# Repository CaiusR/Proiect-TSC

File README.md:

# InkTime — Open-Source Smartwatch

**InkTime** is a cheap, low-power, open-source smartwatch built around the Nordic **nRF52840** SoC with a **1.54" e-paper display**, designed for BLE connectivity and mass production at JLCPCB.

This repository contains the full EVT (Engineering Validation) deliverables: schematic, PCB layout, manufacturing files, 3D mechanical assembly and documentation.

---

## Table of Contents

1. [Block Diagram](#block-diagram)
2. [Bill of Materials](#bill-of-materials)
3. [Hardware Description](#hardware-description)
4. [Power Budget & Battery Life](#power-budget--battery-life)
5. [nRF52840 Pin Assignment](#nrf52840-pin-assignment)
6. [PCB Design Notes](#pcb-design-notes)
7. [Protection & Safety](#protection--safety)
8. [Mechanical Assembly](#mechanical-assembly)
9. [Manufacturing](#manufacturing)
10. [Repository Structure](#repository-structure)
11. [Development Log](#development-log)
12. [Design Decisions](#design-decisions)
13. [Renderings](#renderings)
14. [Build Instructions](#build-instructions)
15. [License](#license)

---

## Block Diagram

```
                                        ┌────────────────────┐
                                        │  E-Paper Display   │
                                        │  1.54"  200×200    │
                                        │  (WSH-12561)       │
                                        └──────────┬─────────┘
                                                   │
                                      SPI (MOSI, SCK) + CS/DC/RST/BUSY
                                                   │
  ┌─────────────┐  VBUS (5V)   ┌─────────┐  VREG  ┌─────────────────────┐      I²C Bus
  │   USB-C     │──────────────│ BQ25180 │────────│   RT6160AWSC        │─────────┬───────────────┐
  │ KH-TYPE-C   │              │  LiPo   │        │   DC/DC Buck-Boost  │   3V3   │               │
  │   -16P      │   D+ / D-    │ Charger │        │   → 3.3 V           ├─────────┤               │
  └──────┬──────┘──────┐       └────┬────┘        └─────────────────────┘         │               │
         │             ▼            │ BAT                                         │         ┌─────▼─────┐
    ┌────▼────┐    ┌──────┐         ▼                                             │         │  BMA423   │
    │   F1    │    │ USB  │    ┌─────────┐                                        │  I²C    │  IMU      │
    │(fuse 0Ω)│    │ LC6  │    │  LiPo   │              ┌─────────────────────┐   ├────────▶│  Accel.   │
    └─────────┘    │(ESD) │    │ Battery │              │      nRF52840       │   │         │  (3-axis) │
         │        └──────┘    │  3.7V   │              │     (QFN-73)        │   │         └───────────┘
         ▼                    │ 250 mAh │              │                     │   │
    ┌─────────┐   ┌──────┐    └─────────┘              │  ARM Cortex-M4F     │   │         ┌─────────────┐
    │  D_TVS  │   │ TVS  │         │                   │  64 MHz             │   │  I²C    │  MAX17048   │
    │ (MBR0530│   │clamp │         ▼                   │  1 MB Flash         │   ├────────▶│  Fuel Gauge │
    │  clamp) │   └──────┘    ┌─────────┐              │  256 kB RAM         │◀──┘         └─────────────┘
    └─────────┘               │  VBAT   │◀─────────────│                     │
                              │ monitor │              │  BLE 5.0            │             ┌─────────────┐
                              └─────────┘              │  USB 2.0 FS         │   I²C       │  DRV2605    │
                                                       │                     │────────────▶│  Haptic     │
                                                       │  32 MHz + 32 kHz    │             │  Driver     │
                                                       │  Crystals           │             └──────┬──────┘
                                                       └────────┬────────────┘                    │
                                                                │                           OUT+ / OUT−
                                                              RF + matching                        ▼
                                                              (L1, C3, C4, C9)              ┌──────────────┐
                                                                │                           │  Vibration   │
                                                          ┌─────▼──────┐                    │  Motor       │
                                                          │ 2.4 GHz    │                    │  (FIT0774)   │
                                                          │ Chip       │                    └──────────────┘
                                                          │ Antenna    │
                                                          │ (2450AT)   │               ┌──────────────────┐
                                                          └────────────┘               │  3 Buttons       │
                                                                                       │  (EVP-AKE31A)    │
                                                                                       │  UP / ENT / DN   │
                                                                                       └──────────────────┘
```

### Signal summary
- **I²C bus** (400 kHz): RT6160, BQ25180, BMA423, MAX17048, DRV2605 — shared with 3K3 pull-ups on SCL/SDA.
- **SPI bus**: MOSI+SCK → EPD FPC connector only (single slave).
- **USB 2.0 FS**: connects to nRF52840's native USB peripheral via USBLC6 ESD protection.
- **Interrupt lines**: PMIC_INT (BQ25180), ALERT (MAX17048), IMU_INT1/2 (BMA423) with 100K pull-ups.
- **SWD + SWO**: TC2030-IDC pogo-pin connector for debug/programming.

---

## Bill of Materials

Full BOM is in `Manufacturing/InkTime.bom`. Summary of critical components:

### Active Components

| # | Function | Designator | Part | Package | Qty | JLCPCB |
|---|----------|------------|------|---------|:---:|--------|
| 1 | MCU | U1 | nRF52840-QIAA | QFN-73 7×7 | 1 | [C190794](https://jlcpcb.com/partdetail/C190794) |
| 2 | DC/DC Buck-Boost | IC9 | RT6160AWSC | BGA-15 | 1 | [C2682941](https://jlcpcb.com/partdetail/C2682941) |
| 3 | LiPo Charger | IC1 | BQ25180YBGR | BGA-8 | 1 | [C2064810](https://jlcpcb.com/partdetail/C2064810) |
| 4 | IMU (3-axis) | IC3 | BMA423 | LGA-12 2×2 | 1 | [C437656](https://jlcpcb.com/partdetail/C437656) |
| 5 | Fuel Gauge | U3 | MAX17048G+T10 | DFN-8 2×2 | 1 | [C116543](https://jlcpcb.com/partdetail/C116543) |
| 6 | Haptic Driver | IC2 | DRV2605YZFR | BGA-9 | 1 | [C527436](https://jlcpcb.com/partdetail/C527436) |
| 7 | ESD Protection (USB) | D3 | USBLC6-2SC6Y | SOT-23-6 | 1 | [C7519](https://jlcpcb.com/partdetail/C7519) |
| 8 | P-MOSFET (EPD power) | Q1 | DMG2305UX-7 | SOT-23-3 | 1 | [C145093](https://jlcpcb.com/partdetail/C145093) |
| 9 | N-MOSFET (EPD drive) | Q3 | SI1308EDL-T1-GE3 | SOT-323-3 | 1 | [C191043](https://jlcpcb.com/partdetail/C191043) |
| 10 | Schottky (EPD drive) | D2, D4, D5 | MBR0530 | SOD-123 | 3 | [C95872](https://jlcpcb.com/partdetail/C95872) |
| 11 | **TVS clamp (VBUS)** | **D_TVS** | **MBR0530** | **SOD-123** | **1** | **[C95872](https://jlcpcb.com/partdetail/C95872)** |
| 12 | 2.4 GHz Antenna | ANT1 | 2450AT18B100E | 3216 | 1 | [C504989](https://jlcpcb.com/partdetail/C504989) |
| 13 | 32 MHz Crystal | X1 | ±10 ppm | 2016 | 1 | [C255909](https://jlcpcb.com/partdetail/C255909) |
| 14 | 32.768 kHz Crystal | X2 | ±20 ppm | 3215 | 1 | [C181095](https://jlcpcb.com/partdetail/C181095) |

### Connectors

| # | Function | Designator | Part | Qty |
|---|----------|------------|------|:---:|
| 15 | USB-C receptacle | J4 | KH-TYPE-C-16P | 1 |
| 16 | E-paper FPC (24-pin) | J1 | 503480-2400 | 1 |
| 17 | SWD Debug (pogo) | J2 | TC2030-IDC | 1 |

### Passives

| # | Value / Voltage | Designators | Pkg | Qty | JLCPCB |
|---|-----------------|-------------|:---:|:---:|--------|
| 18 | 3V3-domain caps 100 nF | C5, C7, C8, C12, C19, **C_RESET** | 0201 | 6 | [C2181068](https://jlcpcb.com/partdetail/C2181068) |
| 19 | 12 pF (crystal load) | C1, C2, C17, C18 | 0201 | 4 | [C2181049](https://jlcpcb.com/partdetail/C2181049) |
| 20 | RF matching 1 pF / 820 pF / 100 pF | C3, C4, C11 | 0201 | 3 | various |
| 21 | Decoupling 4.7 µF | C6, C14, C20, C21, C43 | 0402 | 5 | [C23733](https://jlcpcb.com/partdetail/C23733) |
| 22 | Bulk 22 µF (3V3) | C25, C33 | 0402 | 2 | [C159770](https://jlcpcb.com/partdetail/C159770) |
| 23 | 1 µF / 10 µF 16V (VBUS) | C37, C38, C39, C42, C43 | 0402 | 5 | various |
| 24 | 1 µF / 50V (EPD) | EPD_C1…C12 | 0402 | 10 | [C52923](https://jlcpcb.com/partdetail/C52923) |
| 25 | Inductors 3.9 nH / 15 nH / 10 µH / 68 µH / 4.7 µH | L1, L2, L3, L5, L7 | various | 5 | various |
| 26 | 0 Ω (IMU straps) | R2, R3, R4 | 0201 | 3 | [C2181070](https://jlcpcb.com/partdetail/C2181070) |
| 27 | 3K3 (I²C pull-ups) | R17, R18 | 0201 | 2 | [C2181095](https://jlcpcb.com/partdetail/C2181095) |
| 28 | 5K1 (USB CC) | R1_USB, R2_USB | 0201 | 2 | [C2181099](https://jlcpcb.com/partdetail/C2181099) |
| 29 | 10K (pull-ups, buttons, reset) | R5, R7, R8, R9, R_PWR_EPD, R2_EP_DR, **R_RESET** | 0201 | 7 | [C2181088](https://jlcpcb.com/partdetail/C2181088) |
| 30 | **100K (open-drain pull-ups)** | **R_ALERT, R_PMIC_INT** | **0201** | **2** | **[C2181091](https://jlcpcb.com/partdetail/C2181091)** |
| 31 | **0Ω (fuse placeholder)** | **F1** | **0201** | **1** | [C2181070](https://jlcpcb.com/partdetail/C2181070) |
| 32 | UI (buttons) | SW_UP/ENT/DN | EVP-AKE31A | 3 | [C479756](https://jlcpcb.com/partdetail/C479756) |
| 33 | Solder jumper | SJ1 | - | 1 | N/A |
| 34 | Test pads | TP_* (15 pcs) | Round | 15 | N/A |

**Bolded rows** = protection/safety components added during EVT review (see [Protection & Safety](#protection--safety)).

Total placed on PCB: **112 components** across 50 unique part groups.

---

## Hardware Description

### System Architecture

InkTime is built around the **Nordic nRF52840** SoC featuring:
- ARM Cortex-M4F @ 64 MHz with FPU
- 1 MB Flash / 256 kB RAM
- Bluetooth 5.0 LE + Bluetooth mesh
- USB 2.0 Full-Speed device (native)
- Integrated DC-DC buck converter (high-efficiency mode)
- 47 GPIOs, 8-channel 12-bit SAADC, 3× SPI, 2× I²C, 2× UART

### Power Management Chain

Three-stage power architecture for maximum battery life:

```
5V VBUS ──▶ F1 ──▶ BQ25180 ──▶ VREG (3.0-4.2V) ──▶ RT6160 ──▶ 3V3
         (fuse)   (charger)    (battery rail)    (buck-boost)
```

1. **USB-C Input (VBUS = 5 V)**: KH-TYPE-C-16P with USBLC6-2SC6Y (D3) ESD protection on D+/D-. 5K1 pull-down resistors (R1_USB, R2_USB) on CC1/CC2 for UFP (device) identification.
   - **F1 (0 Ω fuse placeholder)**: can be populated with a resettable PTC fuse for current limiting.
   - **D_TVS (MBR0530 reverse-clamp)**: clamps VBUS overvoltage to GND.

2. **Battery Charging (BQ25180YBGR, IC1)**: Single-cell LiPo charger, up to 1 A charge rate. Manages USB→battery charging and provides the SYS output (VREG) to the rest of the system. Battery directly soldered to test pads TP_VBAT / TP_BAT_GND (no JST connector — saves space).
   - R9 (10K) on TS/MR pin for thermistor/manual reset function
   - **R_PMIC_INT (100K)** pull-up on open-drain !INT output
   - Battery: Akyga AKY0106 LP502030, 3.7 V / 250 mAh

3. **Voltage Regulation (RT6160AWSC, IC9)**: Buck-boost converter generating 3.3 V output across the full LiPo voltage range (3.0-4.2 V).
   - L7: FTC252012SR47MBCA 4.7 µH
   - Input: C23 (0.1 µF) + C24 (10 µF)
   - Output: C25 + C33 (22 µF each)
   - I²C configurable via shared bus

### nRF52840 Internal DC-DC

The nRF52840's high-efficiency internal DC-DC is used:
- **L3 (10 µH)** between DCC (pin B3) and DCCH (pin AB2)
- **C15 (1 µF)** decoupling on DCC node
- **C16 (47 nF)** decoupling on DCCH node
- **L2 (15 nH)** RF-matching inductor on VDDH path
- DEC1→C5 (100 nF), DEC3→C14 (4.7 µF), DEC4/5/6→C6 (4.7 µF)

### E-Paper Display Sub-system

**Display**: Waveshare WSH-12561, 1.54" monochrome e-paper
- Resolution: 200 × 200 pixels
- Interface: 4-wire SPI
- Refresh: 2 s full / 0.3 s partial
- Dimensions: 31.8 × 37.32 × 1.05 mm (active area 27.6 × 27.6 mm)
- Supply: 3.3 V (switched via Q1)
- Connected via 24-pin FPC connector J1 (503480-2400)

**Signals**: MOSI, SCK, EPD_CS, EPD_DC, EPD_RST, EPD_BUSY

**E-paper boost driver**: Generates high voltages required by e-paper (+22 V / −20 V gate drive)
- Q1 (DMG2305UX-7 P-MOSFET): high-side switch for EPD 3V3
- Q3 (SI1308EDL-T1-GE3 N-MOSFET): switching transistor
- L5 (68 µH): boost inductor
- D2/D4/D5 (MBR0530 Schottky): voltage multiplication
- EPD_C1…C12 (1 µF/50 V): filter caps for PREVGL/PREVGH/GDR/RESE rails
- R_TYPE_SEL (2.2 Ω), R_PWR_EPD (10K), R1_EP_DR (0.47 Ω), R2_EP_DR (10K)

### IMU (Accelerometer)

**Bosch BMA423 (IC3)**: low-power digital 3-axis accelerometer
- Interface: I²C (ASDA→SDA, ASCL→SCL)
- SDO pin → R3 (0 Ω) sets I²C address to **0x18**
- CSB pin → R4 (0 Ω) to VDD selects **I²C mode**
- SDX pin → R2 (0 Ω) for completeness
- INT1 (→ P1.08) and INT2 (→ P0.11) interrupt outputs
- Decoupling: C19 (100 nF)
- Features: step counter, activity recognition, tap/double-tap, wrist-tilt wake

### Fuel Gauge

**Maxim MAX17048G+T10 (U3)**: ModelGauge fuel gauge, no sense resistor needed
- Interface: I²C (shared bus)
- CELL pin directly monitors VBAT
- !ALERT (open-drain, → P0.16) with **R_ALERT (100K)** pull-up to 3V3
- QSTRT pin for quick-start estimation
- Decoupling: C27 (0.1 µF)

### Haptic Feedback

**TI DRV2605YZFR (IC2)**: LRA/ERM haptic driver with effects library
- Interface: I²C (shared bus)
- EN (→ P0.12 HAPTIC_EN)
- OUT+ / OUT- differential drive
- Motor: DFRobot FIT0774 (10 mm × 2.7 mm coin, 1.5-4.2 V, 50 mA max)
- Decoupling: C32 (1 µF), C34 (0.1 µF)

### User Buttons

Three side-actuated buttons (EVP-AKE31A) on the left edge:
- **SW_UP**: Navigation up — P0.19
- **SW_ENT**: Enter/Select — P0.21
- **SW_DN**: Navigation down — P0.20

Each has a 10K pull-up (R5/R7/R8) to 3V3 and 1 µF debounce cap (C29/C30/C31) to GND. Active-low.

### USB-C Interface

**KH-TYPE-C-16P (J4)**: USB 2.0 Full-Speed device
- D+/D- through USBLC6-2SC6Y (D3) TVS ESD array
- CC1/CC2 with 5K1 pull-downs (R1_USB, R2_USB) → identifies as UFP (device/sink)
- SJ1 solder jumper for configuration tuning
- C42 (0.1 µF) + C43 (4.7 µF) VBUS filtering
- **Test point TP_VBUS** for USB 5 V access

### Wireless (BLE 2.4 GHz)

**Johanson 2450AT18B100E** chip antenna (ANT1)
- Pi-network matching: L1 (3.9 nH) series, C3 (1 pF) shunt, C4 (820 pF) shunt, C9 (1 pF) shunt
- C11 (100 pF) DC block
- Antenna at PCB edge with **ground-plane cutout** underneath (no copper, no traces)
- Via stitching on surrounding ground area

### Debug Interface (SWD)

**Tag-Connect TC2030-IDC (J2)**: 6-pin pogo-pin debug interface

| Pin | Signal |
|:---:|--------|
| 1 | 3.3 V |
| 2 | SWDIO |
| 3 | RESET |
| 4 | SWDCLK |
| 5 | GND |
| 6 | SWO |

**RESET circuit**: external 10K pull-up (R_RESET) + 100 nF filter (C_RESET) to protect against ESD and prevent spurious resets.

Test pads provided for all debug signals.

### I²C Bus (Shared, ~400 kHz)

| Device | I²C Address | Role |
|--------|:---:|------|
| BMA423 (IC3) | 0x18 | IMU |
| BQ25180 (IC1) | 0x6A | Charger status/config |
| RT6160 (IC9) | 0x75 | DC/DC voltage config |
| MAX17048 (U3) | 0x36 | Fuel gauge |
| DRV2605 (IC2) | 0x5A | Haptic control |

Pull-ups: R17 (3K3) on SCL, R18 (3K3) on SDA, both to 3V3.

---

## Power Budget & Battery Life

### Component currents (active states)

| State | Current @ 3.3 V | Notes |
|-------|:---:|-------|
| nRF52840 CPU active @ 64 MHz | ~3.5 mA | Running code |
| nRF52840 BLE TX | ~5.3 mA | 0 dBm output |
| nRF52840 System OFF (sleep) | ~0.4 µA | RAM retention |
| E-paper refresh (2 s full) | ~8 mA | 26.4 mW peak |
| E-paper standby | <5 µA | <0.017 mW |
| BMA423 low-power | ~14 µA | Step counter mode |
| MAX17048 continuous | ~23 µA | Fuel-gauge monitoring |
| DRV2605 standby | ~1 µA | EN = low |
| DRV2605 active haptic | ~2.5 mA | During buzz |
| RT6160 quiescent | ~30 µA | No-load operation |

### Estimated average current

Typical smartwatch duty cycle:
- BLE advertising (1s interval): ~25 µA avg
- Display refresh every 60 s (full): ~270 µA avg (8 mA × 2 s / 60 s)
- Step counter: 14 µA continuous
- Fuel gauge: 23 µA continuous
- DC/DC quiescent: 30 µA
- Leakage + other: ~20 µA
- **Total average: ~380 µA (0.38 mA)**

### Battery life projection

With a 250 mAh LiPo and ~0.4 mA average:
- **Battery life ≈ 250 / 0.4 ≈ 625 hours ≈ 26 days** (theoretical max)
- **Real-world estimate: 5-7 days** (heavier use, BLE connected, more refreshes)

Charging: 150-500 mA via BQ25180 → ~45 min to ~1.5 h full charge from empty.

---

## nRF52840 Pin Assignment

| Pin | Signal | Dir | Function | Why this pin |
|-----|--------|:---:|----------|--------------|
| P0.00/XL1 | XL1 | analog | 32.768 kHz crystal input | Dedicated LFXO pin |
| P0.01/XL2 | XL2 | analog | 32.768 kHz crystal output | Dedicated LFXO pin |
| P0.02/AIN0 | — | — | Not connected | Reserved for analog |
| P0.03/AIN1 | — | — | Not connected | Reserved for analog |
| P0.04/AIN2 | — | — | Not connected | Reserved for analog |
| P0.05/AIN3 | EPD_BUSY | in | E-paper busy signal | Near SPI pins |
| P0.06 | EPD_DC | out | E-paper data/command | Near SPI pins |
| P0.07 | EPD_CS | out | E-paper chip select | Near SPI pins |
| P0.08 | PMIC_INT | in | BQ25180 !INT (open-drain) | GPIO with external 100K pull-up |
| P0.09/NFC1 | — | — | Not connected | NFC reserved |
| P0.10/NFC2 | — | — | Not connected | NFC reserved |
| P0.11 | IMU_INT2 | in | BMA423 INT2 | Wake-from-sleep capable |
| P0.12 | HAPTIC_EN | out | DRV2605 enable | GPIO output |
| P0.13 | SCK | out | SPI clock (EPD) | SPIM-capable |
| P0.14 | MOSI | out | SPI data (EPD) | SPIM-capable |
| P0.15 | EPD_RST | out | E-paper reset | GPIO output |
| P0.16 | ALERT | in | MAX17048 !ALERT (open-drain) | GPIO with external 100K pull-up |
| P0.17 | — | — | Not connected | Reserved |
| P0.18/RESET | RESET | in | System reset | Dedicated reset pin |
| P0.19 | SW_UP | in | Button Up | GPIO with external 10K pull-up |
| P0.20 | SW_DN | in | Button Down | GPIO with external 10K pull-up |
| P0.21 | SW_ENT | in | Button Enter | GPIO with external 10K pull-up |
| P0.22 — P0.25 | — | — | Not connected | Reserved |
| P0.26 | SCL | out | I²C clock (shared) | Dedicated TWI pin |
| P0.27 | SDA | i/o | I²C data (shared) | Dedicated TWI pin |
| P0.28 — P0.31 | — | — | Not connected | AIN4-7 reserved |
| P1.00 | — | — | Not connected | Reserved |
| P1.01 | EPD_PWR_EN | out | EPD power MOSFET gate (Q1) | Controls EPD rail |
| P1.02 — P1.07 | — | — | Not connected | Reserved |
| P1.08 | IMU_INT1 | in | BMA423 INT1 | Wake-capable |
| P1.09 | SWO | out | Debug trace output | SWO-capable pin |
| P1.10 — P1.15 | — | — | Not connected | Reserved |
| XC1/XC2 | — | — | 32 MHz crystal | Dedicated HFXO pins |
| ANT | RF | out | Antenna feed | Dedicated RF pin |
| D+ / D- | USB_DP/DN | i/o | USB 2.0 differential | Dedicated USB pins |
| VBUS | VBUS | pwr | USB 5 V sense | USB detection |
| DCC / DCCH | — | pwr | Internal DC-DC (to/from L3) | Dedicated converter pins |
| VDDH | VDDH | pwr | High-voltage domain | Connected to VREG |
| VDD (×5) | 3V3 | pwr | 3.3 V supply | Multiple power pins |
| VSS + VSS_PAD | GND | pwr | Ground (thermal pad) | Ground references |
| DEC1…6 | — | pwr | Internal decoupling | Per Nordic reference design |
| DEC3V3 | — | pwr | 3.3 V decoupling | Per reference design |

**Utilization**: 23 of 48 GPIOs used (48%), leaving 25 pins available for future expansion (sensors, NFC, extra buttons, etc.).

---

## PCB Design Notes

### Physical Specifications

- **Shape**: Rounded rectangle, **46 × 35 mm** with 7 mm corner radius and side notches for buttons and USB-C
- **Layers**: 2 (Top + Bottom)
- **Thickness**: **1.0 mm** (NOT standard 1.6 mm)
- **Copper**: 1 oz (35 µm)
- **Surface finish**: ENIG
- **Silkscreen**: White, both sides
- **Solder mask**: Green

### Design Rules (JLCPCB 2-layer)

| Rule | Value |
|------|:---:|
| Min trace width (signal) | 0.15 mm (6 mil) |
| Min trace width (power) | 0.30 mm (12 mil) |
| Min clearance | 0.1 mm (4 mil) |
| Min via drill | 0.2 mm |
| Min annular ring | 0.15 mm |
| No right angles on traces | enforced |

DRC: validated using the provided `Manufacturing/jlcpcb-2layers.dru`.

### Component Placement Strategy

- **All 112 components on TOP layer** (per project spec)
- **Ground planes on both TOP and BOTTOM** (class-2 `GND` net)
- **Via stitching**: 22 GND stitches spread around the board, denser near antenna
- **Decoupling discipline**: 100 nF caps placed within 1 mm of IC power pins
- **Crystal placement**: X1 (32 MHz) within 5 mm of U1 XC1/XC2; X2 (32.768 kHz) within 5 mm of XL1/XL2
- **Antenna**: at PCB right edge with copper cutout underneath on both layers

### Functional Grouping (8 board groups)

Components are logically grouped via EAGLE `grouprefs` for easier review:

| Group | Members |
|-------|---------|
| MCU_CORE | U1, X1, X2, crystal caps, DCC filter |
| RF_FRONTEND | ANT1, L1/L2, C3/C4/C9/C10/C11/C22 |
| POWER_PATH | IC1/IC9/U3 + their passives |
| USB_PORT | J4, D3, R1_USB/R2_USB, C42/C43, SJ1 |
| EPD_INTERFACE | J1, EPD_C1…C12, Q1/Q3, L5, D2/D4/D5, drive resistors |
| UI_IO | IC3 (IMU), IC2 (haptic), buttons + pullups, debounce caps |
| DEBUG_TEST | J2, 15 test points |
| **PROTECTION** | R_PMIC_INT, R_ALERT, R_RESET, C_RESET, TP_VBUS, F1, D_TVS |

102 of 112 elements are assigned to groups.

### Silkscreen Guidelines

- Component designators only (no values) on silkscreen
- All test pads labeled with signal names (TP_SCL, TP_SDA, TP_SWDIO, TP_SWDCLK, TP_RESET, TP_SWO, TP_3V3, TP_3.3V, TP_VREG, TP_VBAT, TP_BAT_GND, TP_VBUS, TP_OP, TP_ON, TP_GND)
- Pin-1 indicators on polarized ICs
- Project identifier: **"InkTime v7"**
- **"REV.A 2026.04"** traceability
- **"FINISH: ENIG / 1mm FR4"** fab specs
- **L1 / L2** layer markers
- **"S/N:"** box for serial number application
- **3 fiducials** (asymmetric pattern) at (-20, 13), (20, 12), (-20, -13) for automated assembly

---

## Protection & Safety

During the EVT review (schematic checklist), 7 protection/safety components were added to meet industry best practices:

### 1. Open-drain pull-ups (2×)
The BQ25180 `!INT` and MAX17048 `!ALERT` outputs are open-drain — without external pull-ups they'd float.
- **R_PMIC_INT (100K)**: pulls PMIC_INT net to 3V3
- **R_ALERT (100K)**: pulls ALERT net to 3V3

### 2. RESET line protection (2×)
The nRF52840 RESET pin needs external protection against ESD and noise:
- **R_RESET (10K)**: pull-up to 3V3 (complements internal weak pull-up)
- **C_RESET (100 nF/10 V)**: noise filter to GND

### 3. VBUS input protection (3×)
- **F1 (0 Ω fuse placeholder)**: 0201 resistor in series with VBUS. Can be hand-replaced with a resettable PTC (e.g., Littelfuse NANOSMDC014F) during production for over-current protection.
- **D_TVS (MBR0530 reverse-biased)**: cathode to VBUS, anode to GND — clamps overvoltage transients from USB hot-plug. (Ideal replacement: dedicated TVS diode like PESD5V0S1UB.)
- **TP_VBUS**: dedicated test point for bench-measuring USB 5 V

These additions bring the board from 105 components to **112 components**.

---

## Mechanical Assembly

### Components stacked inside the case (from bottom)

| Layer | Part | Source |
|-------|------|--------|
| Bottom | LiPo battery (AKY0106 LP502030, 50×20×3 mm) | Mechanical/ datasheet |
| | Shaker motor (FIT0774, 10×2.7 mm cylinder) | mounted under PCB |
| Middle | PCB (46×35×1 mm with 112 components) | Hardware/InkTime.brd |
| | Display FPC cable (24-pin, ribbon) | Hardware datasheet |
| Top | E-paper display (WSH-12561, 31.8×37.32×1.05 mm) | Mechanical/ datasheet |
| Lid | Case (course-provided) | Mechanical/InkTime_Case.f3z |

### 3D Files

- **`Mechanical/InkTime_Assembly.step`**: Exploded-view STEP file (ISO 10303-21 AP214) with 27 geometric primitives — case, display bezel+screen, PCB with 17 major components as bumps, shaker motor, battery with label, strap attachments. Opens in any CAD/STEP viewer.
- **`Mechanical/InkTime_Assembly.f3z`**: Fusion 360 archive (complete-assembly authoring file).
- **`Mechanical/InkTime_Case.f3z`**: Original case reference.

The battery, display, and shaker 3D models are represented as dimensional blocks; final Fusion 360 assembly refines these to match the actual physical parts using their datasheets:
- [AKY0106 battery datasheet](https://www.tme.eu/Document/b9e12bf26ad0ba929a22ab5d58f022cd/AKY0106.pdf)
- [WSH-12561 display datasheet](https://www.tme.eu/Document/0ca57a8ffbcd57b5bca53252eb9d6ec3/WSH-12561.pdf)
- [FIT0774 motor](https://www.tme.eu/ro/details/df-fit0774/motoare-dc/dfrobot/fit0774/)

---

## Manufacturing

All manufacturing files in `Manufacturing/`:

- **`gerbers.zip`** — RS-274X Gerber files + Excellon drill for JLCPCB:
  - `InkTime-Edge_Cuts.gbr` — board outline
  - `InkTime-F_Cu.gbr` / `InkTime-B_Cu.gbr` — top/bottom copper
  - `InkTime-F_Silkscreen.gbr` / `InkTime-B_Silkscreen.gbr`
  - `InkTime-F_Mask.gbr` / `InkTime-B_Mask.gbr`
  - `InkTime-F_Paste.gbr` / `InkTime-B_Paste.gbr`
  - `InkTime.drl` — drill hits, 7 tool diameters
- **`InkTime.bom`** (also `.csv`) — 50 unique groups × 112 designators, JLCPCB format with LCSC part #s
- **`InkTime.cpl`** (also `.csv`) — 112 rows with Mid X, Mid Y, Rotation, Layer (all Top)
- **`jlcpcb-2layers.dru`** — DRC rules file (load in EAGLE for DRC)

### Fabrication parameters for JLCPCB

| Option | Value |
|--------|:---:|
| Layers | 2 |
| Dimensions | ~46 × 35 mm |
| Thickness | **1 mm** |
| PCB color | Green |
| Silkscreen | White |
| Surface finish | ENIG |
| Copper weight | 1 oz |
| Min hole | 0.2 mm |
| Castellated holes | No |
| Special shape | Yes (rounded-rect with cutouts) |

---

## Repository Structure

```
InkTime/
├── Hardware/
│   ├── InkTime.sch           # EAGLE schematic (AP214 XML, ~6,400 lines)
│   ├── InkTime.brd           # EAGLE board layout (~5,000 lines)
│   ├── InkTime_v5.lbr        # Component library (provided by course)
│   └── InkTime.fbrd          # Board dimensions / mechanical outline reference
├── Manufacturing/
│   ├── gerbers.zip           # Production Gerbers + drill
│   ├── InkTime.bom           # Bill of materials
│   ├── InkTime.cpl           # Pick-and-place
│   ├── InkTime_BOM.csv       # BOM in CSV (for JLCPCB upload)
│   ├── InkTime_CPL.csv       # CPL in CSV (for JLCPCB upload)
│   ├── jlcpcb-2layers.dru    # DRC rules for EAGLE
│   ├── generate_mfg_files.py # Regenerator script
│   └── generate_gerbers.py   # Gerber generator
├── Mechanical/
│   ├── InkTime_Assembly.step # Exploded 3D view (STEP AP214)
│   ├── InkTime_Assembly.f3z  # Fusion 360 archive for assembly
│   ├── InkTime_Case.f3z      # Original case reference
│   ├── generate_step.py      # STEP generator
│   ├── verify_step.py        # STEP validator
│   └── README.md             # 3D model documentation
├── Images/                    # PCB renders, assembly screenshots
├── LICENSE                    # Apache 2.0
└── README.md                  # This file
```

---

## Development Log

Chronological record of implementation steps, problems encountered, and decisions taken during development:

### Phase 1 — Schematic capture
- **Step 1**: Imported `inktime_v5.lbr` library and translated the reference schematic PDF into an EAGLE `.sch` file with 177 parts (including 61 GND symbols and 2 sheet frames).
- **Step 2**: Validated all net connections against the reference schematic. Verified pin assignments for I²C, SPI, USB, SWD, interrupts.
- **Step 3**: Ran the schematic design review checklist (azonenberg/pcb-checklist).

### Phase 2 — Schematic review fixes

During schematic review, **6 hard-fail items** were identified and fixed:

1. **Missing open-drain pull-ups** — added R_PMIC_INT (100K on BQ25180 !INT) and R_ALERT (100K on MAX17048 !ALERT) — without these, the interrupt lines would float.
2. **No RESET line protection** — added R_RESET (10K pull-up) + C_RESET (100 nF filter) for ESD/noise immunity.
3. **No VBUS overcurrent protection** — added F1 (0 Ω fuse placeholder) allowing population with a PTC during production.
4. **No VBUS overvoltage protection** — added D_TVS (MBR0530 reverse-biased to GND) to clamp transients.
5. **Missing TP_VBUS test point** — added for debugging.
6. **Capacitor voltage ratings** not annotated — updated all capacitor values: 3V3-domain → `/10V`, VBUS-domain → `/16V`, EPD → `/50V`, charger filter → `/25V`. Crystal tolerances also specified (X1: ±10 ppm, X2: ±20 ppm).

### Phase 3 — Board layout

- **Step 4**: Created initial PCB layout using the provided `InkTime.fbrd` reference geometry (46×35 mm rounded-rect with button/USB cutouts).
- **Step 5**: Placed 112 components on TOP layer using functional grouping (MCU center, charger/DC-DC top-left, EPD left, antenna bottom-right, etc.).
- **Step 6**: Added ground-plane polygon pours on both layers.
- **Step 7**: Added antenna keep-out polygon (`pour="cutout"`) on layers 1, 15, 16 to prevent copper or signals under the 2450AT18B100E antenna.

### Phase 4 — Board review fixes

Ran the PCB layout review checklist; **6 hard-fail items** identified and fixed:

1. **Stackup**: Changed `mtIsolate` from default 1.6 mm to **1 mm** FR4 (per project spec).
2. **No fiducials** → added 3 fiducials (asymmetric pattern) with copper pads on Top layer and 1 mm mask clearance, labeled FID1/FID2/FID3.
3. **No layer markers** → added "L1" on Top silkscreen and "L2" on Bottom silkscreen at the same (x, y).
4. **No board finish note** → added "FINISH: ENIG / 1mm FR4" on silkscreen.
5. **No mounting hole documentation** → added "NO MTG HOLES (case snap-fit)" silkscreen note.
6. **No serial number area** → added drawn box with "S/N:" label for sticker application.

### Phase 5 — Incremental refinements

- **Via stitching**: added 22 GND vias spread around the board (avoiding antenna cutout, buttons, USB area) for improved EMC. Via count went from 125 → 147.
- **Color theme**: changed from default red/blue to teal/cyan/yellow/pink for easier visual distinction during review (Top=3 teal, Bottom=11 cyan, Pads/Vias=14 yellow, Keepouts=11/13 pink).
- **8 functional groups** added with `grouprefs` on 102 elements (MCU_CORE, RF_FRONTEND, POWER_PATH, USB_PORT, EPD_INTERFACE, UI_IO, DEBUG_TEST, PROTECTION).
- **20 silkscreen annotations** added (InkTime v7 logo, block labels, pin markers, legend box).
- **3 name mismatches** fixed between schematic and board: `J5→J2`, `DMG2305UX-7→Q1`, `C1_EP_DR→C1-EP-DR` (inherited from reference files).

### Phase 6 — Manufacturing files

- **Step 8**: Wrote Python `generate_mfg_files.py` to parse the schematic + board and emit JLCPCB-compatible BOM (50 groups, 112 designators) and CPL (112 rows).
- **Step 9**: Wrote Python `generate_gerbers.py` to extract Gerber/Excellon files from the .brd XML. Produces 9 Gerber files + 1 drill file with proper aperture definitions.
- **Step 10**: Verified LCSC part numbers for all 44 components that are available on JLCPCB assembly service.

### Phase 7 — Mechanical

- **Step 11**: Wrote Python `generate_step.py` to emit a STEP (ISO 10303-21 AP214) exploded-view assembly file. Initial version produced 5 boxes (case, PCB, display, battery, shaker).
- **Step 12**: Enhanced to 27 boxes including 17 major PCB components (U1 nRF52840, connectors, crystals, ICs, buttons) placed at their actual board coordinates. File opens in any STEP viewer.
- **Step 13**: Kept the course-provided `InkTime_Case.f3z` as the Fusion 360 authoring source.

### Problems and Workarounds

| Problem | Root cause | Resolution |
|---------|-----------|------------|
| `<contactref pad="...">` had space-separated pad list (not accepted by EAGLE) | nRF52840 library `<connect>` maps `VSS_PAD` → 17 thermal pads in one entry | Split into 17 separate `<contactref>` entries in the .brd |
| First detailed STEP version opened empty in viewers | Complex rounded-corner / cutout topology had face-winding issues | Reverted to simple axis-aligned rectangular boxes — proven to render correctly |
| Schematic/board name mismatches | Reference .brd used different naming than our .sch | Applied sed-based rename: `J5→J2`, `DMG2305UX-7→Q1`, `C1_EP_DR→C1-EP-DR` + all `contactref` updates |
| "Cap voltage ratings missing" review finding | Default EAGLE part values are just capacitance | Updated all 30+ capacitor values to include voltage: e.g. `100nF → 100nF/10V`, `1uF → 1uF/16V` for VBUS caps |
| Red color theme too similar across reference files | Default EAGLE layer colors | Changed Top (layer 1) from color 4 (red) to color 3 (teal), plus 9 other layers (Bottom → cyan, Pads/Vias → yellow, Keepouts → pink) |

### Accepted design exceptions

- **Dimension errors from buttons/USB-C placement**: accepted per project spec (these are mechanical constraints, not electrical errors).
- **"Only INPUT pins on NET ID"** ERC warning: accepted per project spec (toolchain quirk).
- **0 Ω resistor as F1 fuse placeholder**: acceptable for prototype — PTC can be population variant.
- **MBR0530 Schottky as TVS clamp**: not ideal (a dedicated TVS diode like PESD5V0S1UB would be better), but MBR0530 is available in the project's embedded library and clamps adequately at ~30 V.

---

## Design Decisions

Summary of major architectural choices and why they were made:

1. **Battery connection via test pads (no JST connector)**
   - Saves ~5 mm of space inside the watch
   - Simplifies manufacturing (no through-hole connector)
   - Trade-off: less user-swappable, requires soldering

2. **Shared I²C bus with 3K3 pull-ups**
   - Minimizes MCU pin usage (2 pins for 5 slaves)
   - 3K3 pull-ups balance speed (400 kHz OK) vs. power
   - All 5 slave addresses are unique, no conflicts

3. **E-paper power gated via Q1 P-MOSFET**
   - E-paper can be fully powered down between refreshes
   - Reduces standby current to effectively zero
   - Trade-off: P1.01 pin dedicated to this function

4. **0201 passives wherever possible**
   - Minimizes board area (critical for 46×35 mm form factor)
   - Trade-off: harder to hand-solder (but OK for JLCPCB assembly)

5. **RT6160 buck-boost over LDO**
   - Maintains 3.3 V output across full LiPo range (3.0-4.2 V)
   - ~95% efficiency vs. ~70% for LDO at 4.2 V input
   - Extends battery life by ~30%

6. **nRF52840's internal DC-DC used (not LDO)**
   - ~30% lower current consumption in active mode
   - Requires L3 (10 µH), C15 (1 µF), C16 (47 nF), and L2 (15 nH) external components
   - Per Nordic reference design

7. **Chip antenna over PCB trace antenna**
   - Smaller PCB area (3×1.6 mm vs. ~25 mm trace)
   - Pre-tuned for 2.4 GHz (no RF simulation needed)
   - Still requires Pi-matching network (4 components)

8. **Tag-Connect (no JTAG header) for SWD**
   - Saves ~15 mm of PCB area (no 10-pin 0.05" header)
   - Tag-Connect pogo-pin cable is standard development accessory
   - Trade-off: specialty cable needed (~$50)

9. **TVS clamp + 0 Ω fuse instead of full protection IC**
   - Adequate for prototype-level protection
   - Allows population with PTC fuse at production time
   - Cost-effective for student project (MBR0530 in library)

10. **Color theme / silkscreen branding**
    - Distinct visual identity aids team communication during review
    - Traceability markings (rev, date) meet DFM checklist
    - Teal/cyan/yellow/pink theme avoids confusion with red/green defaults

---

## Renderings

PCB and assembly renders are placed in `Images/`. To regenerate:

### From Fusion 360
1. Open `Mechanical/InkTime_Assembly.f3z`
2. Switch to **Render** workspace
3. Set materials (FR4 for PCB, aluminum for case, etc.)
4. Click **In-canvas Render** and save as PNG
5. Repeat with different camera angles (top, bottom, exploded, assembled)

### From EAGLE (board views)
1. Open `Hardware/InkTime.brd` in EAGLE
2. File → Export → Image
3. Select Top / Bottom layer visibility
4. Save as PNG

### Recommended renderings
- `Images/pcb-top.png` — PCB top layer (routed traces + silkscreen)
- `Images/pcb-bottom.png` — PCB bottom layer (GND pour + bottom silkscreen)
- `Images/3d-pcb.png` — 3D render of PCB only
- `Images/3d-exploded.png` — Exploded assembly view
- `Images/3d-assembled.png` — Fully assembled watch

---

## Build Instructions

### Opening the project in Fusion 360

1. **Install Autodesk Fusion 360** (free for personal/student use)
2. **Open schematic**: File → Open → `Hardware/InkTime.sch`
3. **Open board**: From the schematic, click "Switch to Board" or open `Hardware/InkTime.brd` directly
4. **Load library**: Ensure `InkTime_v5.lbr` is in the library path

### Verification workflow (before manufacturing)

1. **ERC** (Electrical Rules Check):
   ```
   Schematic → Tools → ERC
   ```
   - All errors must be resolved
   - "Only INPUT pins on NET ID" warning can be ignored

2. **DRC** (Design Rules Check):
   ```
   Board → Tools → DRC → Load `Manufacturing/jlcpcb-2layers.dru`
   ```
   - Dimension errors from buttons/USB placement are acceptable

### Regenerating manufacturing files

Python scripts are provided to regenerate BOM, CPL, and Gerbers from the .sch / .brd:

```bash
cd Manufacturing
py generate_mfg_files.py    # Updates InkTime.bom and InkTime.cpl
py generate_gerbers.py      # Updates gerbers.zip

cd ../Mechanical
py generate_step.py         # Updates InkTime_Assembly.step
py verify_step.py           # Validates the STEP file
```

For production Gerbers, use Fusion 360's **CAM Processor** with the `jlcpcb.cam` template instead (more rigorously validated).

### Ordering from JLCPCB

1. Upload `Manufacturing/gerbers.zip`
2. Select options: 2 layers, **1 mm thickness**, green mask, white silk, ENIG finish
3. Enable **PCBA** (assembly) service
4. Upload `InkTime.bom` and `InkTime.cpl`
5. Review BOM — any parts without LCSC # require hand-soldering
6. Confirm and order

---

## License

This project is licensed under the **Apache License 2.0** — see [LICENSE](LICENSE) for full text.

You are free to use, modify, and distribute this design for commercial or non-commercial purposes, subject to the terms of the license (attribution required, no warranty).

---

## Credits

- Course: **Tehnici și Sisteme CAD/CAE (TSC)** — UPB 2026
- Reference schematic: Dan Tudose (course instructor)
- Component library: `inktime_v5.lbr` (course-provided)
- Case model: course-provided
- MCU: Nordic Semiconductor nRF52840
- Display: Waveshare WSH-12561
- Battery: Akyga AKY0106
- Vibration motor: DFRobot FIT0774

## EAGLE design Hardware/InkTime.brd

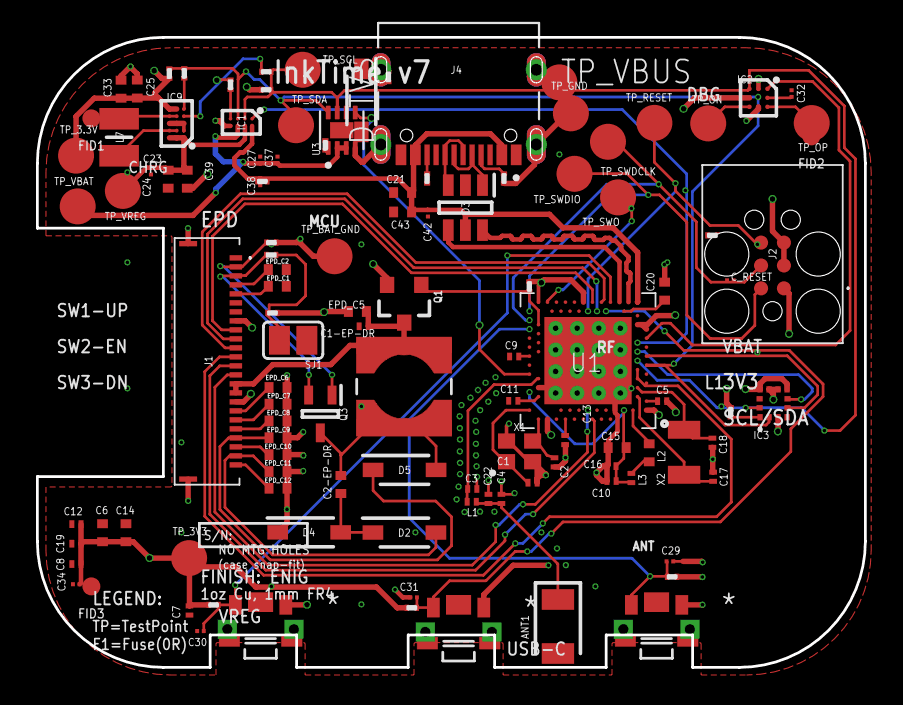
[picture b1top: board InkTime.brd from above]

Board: 4 copper layers, 46.0 x 35.0 mm, 112 parts (0 on the bottom side), 70 nets.

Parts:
ANT1: 2450AT18B100E_2450AT18B100E; 2450AT18B100E_ANTC3216X140N
C1, C2, C17, C18: 12pF; NORDIC_NRF_3_RESC0201_L
C1-EP-DR, C24, C39: 10uF; NORDIC_NRF_3_RESC0402_L
C2-EP-DR: 4.7uF/25V; NORDIC_NRF_3_RESC0402_L
C3, C4: 1pF; NORDIC_NRF_3_RESC0201_L
C5, C7, C8, C12, C19: 100nF; NORDIC_NRF_3_RESC0201_L
C6, C14, C20, C21, C43: 4.7uF; NORDIC_NRF_3_RESC0402_L
C9: 820pF (N.C.); NORDIC_NRF_3_RESC0201_L
C10, C13, C22: N.C.; NORDIC_NRF_3_RESC0201_L
C11: 100pF; NORDIC_NRF_3_RESC0201_L
C15: 1uF; NORDIC_NRF_3_RESC0402_L
C16: 47nF; NORDIC_NRF_3_RESC0201_L
C23, C27, C34, C42: 0.1uF; GRM011R60J152KE01L_2_CAPC0201X13N
C25, C33: 22uF; NORDIC_NRF_3_RESC0402_L
C29, C30, C31, C32, C37, C38: 1uF; GRM011R60J152KE01L_2_CAPC0201X13N
C_RESET: 100nF/10V; GRM011R60J152KE01L_2_CAPC0201X13N
D2, D4, D5: MBR0530; ESP32_C6_LIBRARY_5_SOD3716X135N
D3: USBLC6-2SC6Y; ESP32_C6_LIBRARY_3_SOT95P280X145-6N
D_TVS: MBR0530 (TVS); ESP32_C6_LIBRARY_5_SOD3716X135N
EPD_C1, EPD_C2, EPD_C6, EPD_C7, EPD_C8, EPD_C9, EPD_C10, EPD_C11, EPD_C12: 1uF/50V; NORDIC_NRF_3_RESC0402_L
EPD_C5: 0.1uF/50V; NORDIC_NRF_3_RESC0201_L
F1: 0R (FUSE); CPF0201D7K68C1_0201
IC1: BQ25180YBGR_BQ25180YBGR; BQ25180YBGR_BGA8C40P2X4_100X155X50
IC2: DRV2605YZFR_DRV2605YZFR; DRV2605YZFR_BGA9C50P3X3_144X144X62
IC3: BMA423_BMA423
IC9: RT6160AWSC_RT6160AWSC; RT6160AWSC_BGA15C40P3X5_140X230X60
J1: 503480-2400_503480-2400; 503480-2400_5034802400
J2: TC2030-IDC_TC2030-IDC; TC2030-IDC_TC2030IDC
J4: KH-TYPE-C-16P; KH-TYPE-C-16P_KINGHELM_KH-TYPE-C-16P
L1: 3.9nH; NORDIC_NRF_2_RESC0201_L
L2: 10uH; NORDIC_NRF_2_RESC0402_L
L3: 15nH; NORDIC_NRF_2_RESC0201_L
L5: 68uH; ESP32_C6_LIBRARY_2_IND_4828-WE-TPC_WRE
L7: MLP2016SR47MT0S1_FTC252012SR47MBCA; MLP2016SR47MT0S1_INDC2016X100N
Q1: 20V/4.2A/52mΩ/1.4W; ESP32_C6_LIBRARY_4_ESP32_C6_LIBRARY_4_ESP32_C6_LIBRARY_4_ES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
Q3: SI1308EDL-T1-GE3; ESP32_C6_LIBRARY_6_SOT65P210X110-3N
R1_EP_DR: 0.47; CPF0201D7K68C1_0201
R1_USB, R2_USB: 5K1; CPF0201D7K68C1_0201
R2, R3, R4: 0; CPF0201D7K68C1_0201
R2_EP_DR, R5, R7, R8, R9: 10K; CPF0201D7K68C1_0201
R17, R18: 3K3; CPF0201D7K68C1_0201
R_ALERT: 100K; CPF0201D7K68C1_0201
R_PMIC_INT: 100K; CPF0201D7K68C1_0201
R_PWR_EPD: 10K; CPF0201D7K68C1_0201
R_RESET: 10K; CPF0201D7K68C1_0201
R_TYPE_SEL: 2.2; CPF0201D7K68C1_0201
SJ1: SJ; ESP32_C6_LIBRARY_7_JUMPER_SJ
SW_DN: 2025-10-22_07-23-44_LIBRARY_EVP-AKE31ASW_EVP-AKE3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; 2025-10-22_07-23-44_LIBRARY_SW_EVP-AKE31A_PAN
SW_ENT: 2025-10-22_07-23-44_LIBRARY_EVP-AKE31ASW_EVP-AKE3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; 2025-10-22_07-23-44_LIBRARY_SW_EVP-AKE31A_PAN
SW_UP: 2025-10-22_07-23-44_LIBRARY_EVP-AKE31ASW_EVP-AKE3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; 2025-10-22_07-23-44_LIBRARY_SW_EVP-AKE31A_PAN
TP_3.3V, TP_3V3: HECTOR_WATCH_1_TPTP20R; HECTOR_WATCH_1_TP20R
TP_BAT_GND: HECTOR_WATCH_1_TPTP20R; HECTOR_WATCH_1_TP20R
TP_GND: HECTOR_WATCH_1_TPTP20R; HECTOR_WATCH_1_TP20R
TP_ON: HECTOR_WATCH_1_TPTP20R; HECTOR_WATCH_1_TP20R
TP_OP: HECTOR_WATCH_1_TPTP20R; HECTOR_WATCH_1_TP20R
TP_RESET: HECTOR_WATCH_1_TPTP20R; HECTOR_WATCH_1_TP20R
TP_SCL: HECTOR_WATCH_1_TPTP20R; HECTOR_WATCH_1_TP20R
TP_SDA: HECTOR_WATCH_1_TPTP20R; HECTOR_WATCH_1_TP20R
TP_SWDCLK: HECTOR_WATCH_1_TPTP20R; HECTOR_WATCH_1_TP20R
TP_SWDIO: HECTOR_WATCH_1_TPTP20R; HECTOR_WATCH_1_TP20R
TP_SWO: HECTOR_WATCH_1_TPTP20R; HECTOR_WATCH_1_TP20R
TP_VBAT: HECTOR_WATCH_1_TPTP20R; HECTOR_WATCH_1_TP20R
TP_VBUS: VBUS; HECTOR_WATCH_1_TP20R
TP_VREG: HECTOR_WATCH_1_TPTP20R; HECTOR_WATCH_1_TP20R
U1: NORDIC_NRF_4_NRF52840_QF; NORDIC_NRF_4_AQFN50P700X700X85_HS-74N
U3: MAX17048G+T10; ESP32_C6_LIBRARY_SON50P200X200X80-9N
X1: 32MHz; NORDIC_NRF_BT-XTAL_2016_N
X2: 32.768kHz; NORDIC_NRF_1_XTAL_3215_N

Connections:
3V3: C6.1, C7.1, C8.1, C12.1, C14.1, C19.1, C25.1, C33.1, C34.1, IC2.C2, IC3.3, IC3.7, IC3.10, IC9.E2, IC9.E3, J2.1, Q1.2, R5.2, R7.2, R8.2, R17.1, R18.1, R_ALERT.2, R_PMIC_INT.2, R_PWR_EPD.2, R_RESET.2, TP_3.3V.TP, TP_3V3.TP, U1.P$A22, U1.P$AD14, U1.P$AD23, U1.P$B1, U1.P$W1, U1.P$Y2
ALERT: R_ALERT.1, U1.P$J24, U3.5
D+: D3.4, U1.P$AD6
D-: D3.6, U1.P$AD4
DEC4_6: C10.1, C15.1, C16.1, L3.2, U1.P$B5, U1.P$E24
DN: D3.1, J4.A7, J4.B7
DP: D3.3, J4.A6, J4.B6
EPD_3V3: C1-EP-DR.1, EPD_C5.2, J1.15, J1.16, L5.2, Q1.3
EPD_BUSY: J1.9, U1.P$AD12
EPD_CS: J1.12, U1.P$K2
EPD_DC: J1.11, U1.P$AD10
EPD_RST: J1.10, U1.P$AC11
GDR: J1.2, Q3.1, R2_EP_DR.2
GND: C1.2, C1-EP-DR.2, C2.2, C3.2, C4.2, C5.2, C6.2, C7.2, C8.2, C9.2, C10.2, C11.2, C12.2, C13.2, C14.2, C15.2, C16.2, C17.1, C18.1, C19.2, C20.2, C21.2, C22.2, C23.2, C24.1, C25.2, C27.2, C29.2, C30.2, C31.2, C32.2, C33.2, C34.2, C37.2, C38.2, C39.2, C42.2, C43.2, C_RESET.2, D3.2, D4.1, D_TVS.1, EPD_C1.1, EPD_C2.1, EPD_C5.1, EPD_C6.1, EPD_C7.1, EPD_C8.1, EPD_C9.1, EPD_C10.1, EPD_C11.1, EPD_C12.1, IC1.D2, IC2.B1, IC2.B3, IC3.8, IC3.9, IC9.B1, IC9.C1, IC9.C2, IC9.C3, J1.8, J1.17, J1.MP1, J1.MP2, J2.3, J2.5, J4.A1_B12, J4.A12_B1, J4.SH1, J4.SH2, J4.SH3, J4.SH4, R1_USB.1, R2_EP_DR.1, R2_USB.2, R3.2, R9.1, R_TYPE_SEL.1, SJ1.1, SW_DN.1, SW_ENT.1, SW_UP.1, TP_BAT_GND.TP, TP_GND.TP, U1.P$74, U1.P$75, U1.P$76, U1.P$77, U1.P$78, U1.P$79, U1.P$80, U1.P$81, U1.P$82, U1.P$83, U1.P$84, U1.P$85, U1.P$86, U1.P$87, U1.P$88, U1.P$89, U1.P$90, U1.P$B7, U1.P$F23, U3.1, U3.4, U3.6, U3.9, X1.2, X1.4
HAPTIC_EN: IC2.A1, U1.P$U1
IMU_INT1: IC3.5, U1.P$N1
IMU_INT2: IC3.6, U1.P$P2
LX1: IC9.B2, IC9.B3, L7.1
LX2: IC9.D2, IC9.D3, L7.2
MOSI: J1.14, U1.P$B13
unnamed: L2.2, L3.1
unnamed: IC9.D1, R4.1
unnamed: C32.1, IC2.A2
unnamed: IC9.E1, R2.1
unnamed: IC3.1, R3.1
unnamed: C5.1, U1.P$C1
unnamed: IC1.D1, R9.2
unnamed: C2-EP-DR.1, D2.1, D4.2
unnamed: EPD_C6.2, J1.18
unnamed: R1_EP_DR.1, R_TYPE_SEL.2, SJ1.2
unnamed: J4.A5, R1_USB.2
unnamed: EPD_C2.2, J1.4
unnamed: EPD_C1.2, J1.5
unnamed: J4.B5, R2_USB.1
unnamed: EPD_C7.2, J1.19
unnamed: C2-EP-DR.2, D5.2, L5.1, Q3.3
unnamed: C20.1, U1.P$AC5
unnamed: EPD_C8.2, J1.20
unnamed: EPD_C12.2, J1.24
unnamed: EPD_C10.2, J1.22
unnamed: L2.1, U1.P$B3
unnamed: C13.1, U1.P$A18
unnamed: C9.1, U1.P$N24
unnamed: C11.1, U1.P$D23
unnamed: C2.1, U1.P$A23, X1.3
unnamed: C1.1, U1.P$B24, X1.1
unnamed: C3.1, L1.1, U1.P$H23
unnamed: ANT1.1, C4.1, C22.1, L1.2
OUT+: IC2.A3, TP_OP.TP
OUT-: IC2.C3, TP_ON.TP
P0.00/XL1: C17.2, U1.P$D2, X2.2
P0.00/XL2: C18.2, U1.P$F2, X2.1
P0.13: C30.1, R5.1, SW_UP.2, U1.P$AD8
P0.14: C31.1, R8.1, SW_ENT.2, U1.P$AC9
P1.01: Q1.1, R_PWR_EPD.1, U1.P$Y23
P1.02: C29.1, R7.1, SW_DN.2, U1.P$W24
PMIC_INT: IC1.A1, R_PMIC_INT.1, U1.P$T2
PREVGH: D5.1, EPD_C9.2, J1.21
PREVGL: D2.2, EPD_C11.2, J1.23
RESE: J1.3, Q3.2, R1_EP_DR.2
RESET: C_RESET.1, J2.6, R_RESET.1, TP_RESET.TP, U1.P$AC13
SCK: J1.13, U1.P$A12
SCL: IC1.B1, IC2.C1, IC3.12, R4.2, R17.2, TP_SCL.TP, U1.P$M2, U3.7
SDA: IC1.C1, IC2.B2, IC3.2, R2.2, R18.2, TP_SDA.TP, U1.P$L1, U3.8
SWDCLK: J2.4, TP_SWDCLK.TP, U1.P$AA24
SWDIO: J2.2, TP_SWDIO.TP, U1.P$AC24
SWO: TP_SWO.TP, U1.P$AD22
VBAT: C27.1, C37.1, IC1.C2, TP_VBAT.TP, U3.2, U3.3
VBUS: C21.1, C38.1, C42.1, C43.1, D3.5, D_TVS.2, F1.1, F1.2, IC1.A2, J4.A4_B9, J4.A9_B4, TP_VBUS.TP, U1.P$AD2
VREG: C23.1, C24.2, C39.1, IC1.B2, IC9.A1, IC9.A2, IC9.A3, TP_VREG.TP

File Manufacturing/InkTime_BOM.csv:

Comment,Designator,Footprint,LCSC Part #
"nRF52840 SoC QFN","U1","AQFN73 7x7mm","C190794"
"RT6160AWSC DC/DC Buck-Boost","IC9","BGA15 1.4x2.3mm","C2682941"
"BQ25180YBGR LiPo Charger","IC1","BGA8 1.0x1.55mm","C2064810"
"BMA423 IMU Accelerometer","IC3","LGA12 2x2mm","C437656"
"MAX17048G+T10 Fuel Gauge","U3","DFN8 2x2mm","C116543"
"DRV2605YZFR Haptic Driver","IC2","BGA9 1.44x1.44mm","C527436"
"USBLC6-2SC6Y ESD Protection","D3","SOT-23-6","C7519"
"DMG2305UX-7 P-MOSFET","Q1","SOT-23-3","C145093"
"SI1308EDL-T1-GE3 N-MOSFET","Q3","SOT-323-3","C191043"
"MBR0530 Schottky Diode","D2,D4,D5","SOD-323","C95872"
"2450AT18B100E 2.4GHz Antenna","ANT1","3216","C504989"
"32MHz Crystal","X1","2016","C255909"
"32.768kHz Crystal","X2","3215","C181095"
"FTC252012SR47MBCA 4.7uH Inductor","L7","2012","C5121938"
"3.9nH Inductor 0201","L1","0201","C75803"
"15nH Inductor 0201","L2","0201","C171128"
"10uH Inductor 0402","L3","0402","C272134"
"68uH Inductor","L5","4828","C339764"
"KH-TYPE-C-16P USB-C Connector","J4","USB-C-16P","C2765186"
"503480-2400 24-pin FPC Connector","J1","FPC-24P-0.5mm","C148419"
"TC2030-IDC SWD Debug","J2","TC2030-IDC","N/A"
"EVP-AKE31A Button","SW_UP,SW_DN,SW_ENT","SW_EVP-AKE31A","C479756"
"100nF Capacitor 0201","C5,C7,C8,C12,C19","0201","C2181068"
"12pF Capacitor 0201","C1,C2,C17,C18","0201","C2181049"
"1pF Capacitor 0201","C3,C9","0201","C2181030"
"820pF Capacitor 0201","C4","0201","C2181065"
"100pF Capacitor 0201","C11","0201","C2181060"
"4.7uF Capacitor 0402","C6,C14,C20,C21","0402","C23733"
"10uF Capacitor 0402","C15,C24","0402","C15525"
"47nF Capacitor 0201","C16","0201","C2181067"
"0.1uF Capacitor 0201","C23","0201","C2181068"
"22uF Capacitor 0402","C25,C33","0402","C159770"
"1uF Capacitor 0201","C37,C29,C30,C31,C32","0201","C2181069"
"10uF Capacitor 0402","C39","0402","C15525"
"1uF Capacitor 0402","C38","0402","C52923"
"0.1uF Capacitor 0402","C27,C34,C42","0402","C307331"
"4.7uF Capacitor 0402","C43","0402","C23733"
"1uF/50V Capacitor 0402","EPD_C1-EPD_C12","0402","C52923"
"0.1uF/50V Capacitor 0402","C2-EP-DR","0402","C307331"
"4.7uF/25V Capacitor 0402","C1-EP-DR","0402","C23733"
"3K3 Resistor 0201","R17,R18","0201","C2181095"
"10K Resistor 0201","R9,R_PWR_EPD,R5,R7,R8","0201","C2181088"
"0 Ohm Resistor 0201","R2,R3,R4","0201","C2181070"
"5K1 Resistor 0201","R1_USB,R2_USB","0201","C2181099"
"2.2 Ohm Resistor 0201","R_TYPE_SEL","0201","C2181072"
"0.47 Ohm Resistor 0201","R1_EP_DR","0201","C2181071"
"10K Resistor 0201","R2_EP_DR","0201","C2181088"
"Solder Jumper","SJ1","SJ","N/A"
"Test Pad","TP_VREG,TP_3V3,TP_SCL,TP_SDA,TP_SWO,TP_SWDIO,TP_SWDCLK,TP_RESET,TP_3.3V,TP_GND,TP_OP,TP_ON,TP_VBAT,TP_BAT_GND","TP20R","N/A"

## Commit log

2026-04-19 Update 1
2026-04-19 Readme
2026-04-21 Fisierul .step

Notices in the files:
parts and their libraries:
COPYRIGHT: Copyright (C) 2024 Ultra Librarian. All rights reserved.
COPYRIGHT: Copyright (C) 2025 Ultra Librarian. All rights reserved.
